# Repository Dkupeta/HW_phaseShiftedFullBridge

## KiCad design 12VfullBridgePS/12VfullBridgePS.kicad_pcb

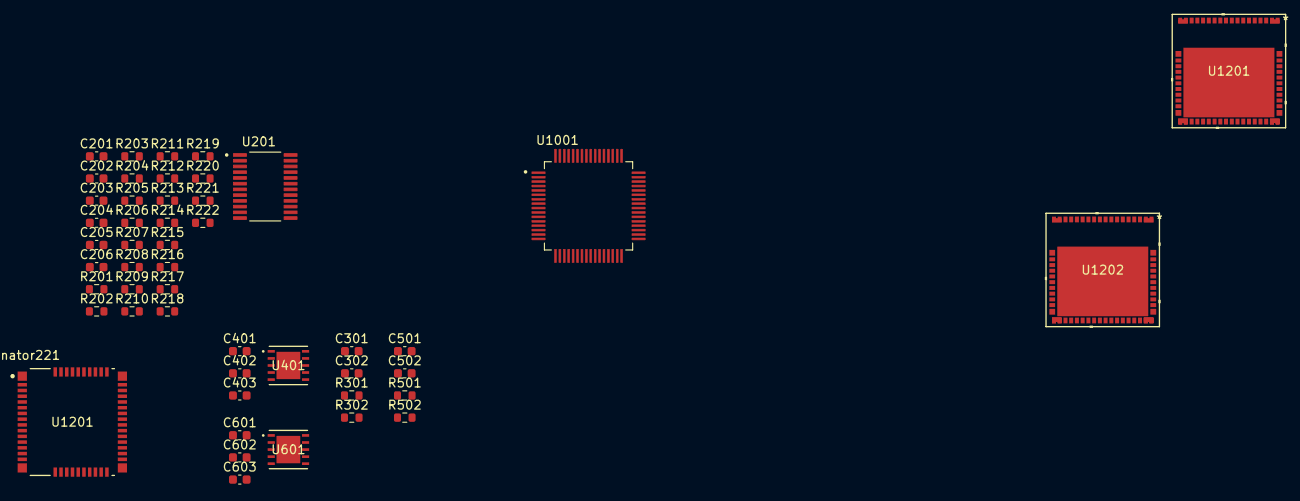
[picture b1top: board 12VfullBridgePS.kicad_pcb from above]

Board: 4 copper layers, 49 parts (0 on the bottom side), 33 nets, no tracks yet.

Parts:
C201: 330pF; C_0603_1608Metric
C202: 0.01uF; C_0603_1608Metric
C203, C206, C301, C401, C501, C601: 1uF; C_0603_1608Metric
C204: 0.047uF; C_0603_1608Metric
C205: 820pF; C_0603_1608Metric
C302, C402, C403, C502, C602, C603: 0.1uF; C_0603_1608Metric
R201, R218, R220: 10k; R_0603_1608Metric
R202: 10; R_0603_1608Metric
R203: 19.1k; R_0603_1608Metric
R204: 100; R_0603_1608Metric
R205: 18.2K; R_0603_1608Metric
R206: 1k; R_0603_1608Metric
R207, R208: 10K; R_0603_1608Metric
R209: 60.4K; R_0603_1608Metric
R210: 20K; R_0603_1608Metric
R211, R213, R215, R217, R219: DNP; R_0603_1608Metric
R212, R214, R216: 13k; R_0603_1608Metric
R221, R222, R301, R302, R501, R502: 0; R_0603_1608Metric
U201: UCC28951QPWRQ1
U401, U601: UCC27212AQDDARQ1; 8-PowerSOIC
U1001: F280048CPMQR; QFP50P1200X1200X160-64N
U1201: LMG3522R030QRQSRQ1; LMG3522R030QRQSRQ1-52-VQFN
U1201#2, U1202: XLMG3422R050RQZT; VQFN-54_12x12

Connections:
/DRV1/10V: C301.1, C302.1, C401.1, C402.1, C501.1, C502.1, C601.1, C603.1, U401.1 (VDD), U601.1 (VDD)
/DRV_E: R501.2, R502.2
/DRV_F: R301.2, R302.2
/PWMA: U201.22 (OUTA), U401.7 (HI)
/PWMC: U201.20 (OUTC), U601.7 (HI)
/PWMD: U201.19 (OUTD), U601.8 (LI)
/SW_AB: C403.1, U401.4 (HS)
/SW_CD: C602.1, U601.4 (HS)
/TMS_mcu/refGND: U1001.5 (VSS), U1001.21 (VSSA), U1001.26 (VSS), U1001.45 (VSS), U1001.55 (VSS_SW), U1001.58 (VSS)
/controller/ADEL: R217.1, R218.2, R221.1, U201.14 (ADEL)
/controller/ADELEF: R219.1, R220.2, R222.1, U201.13 (ADELEF)
/controller/CS_FLT: C205.2, R204.1, R221.2, R222.2, U201.15 (CS)
/controller/DCM: R203.1, R206.2, U201.12 (DCM)
/controller/DELAB: R215.1, R216.2, U201.6 (DELAB)
/controller/DELCD: R213.1, R214.2, U201.7 (DELCD)
/controller/DELEF: R211.1, R212.2, U201.8 (DELEF)
/controller/EA+: R207.2, R208.1, U201.2 (EA+)
/controller/VREF: C203.2, R203.2, R205.1, R207.1, R211.2, R213.2, R215.2, R217.2, R219.2, U201.1 (VREF)
FB: C201.2, C202.2, U201.3 (EA-)
GNDREF: C201.1, C203.1, C204.1, C205.1, C206.2, C301.2, C302.2, C401.2, C402.2, C501.2, C502.2, C601.2, C603.2, R201.1, R206.1, R208.2, R209.2, R210.1, R212.1, R214.1, R216.1, R218.1, R220.1, U201.4 (COMP), U201.21 (OUTB), U201.24 (GND), U401.8 (LI), U401.9 (VSS), U401.11 (POWERPAD), U601.9 (VSS), U601.11 (POWERPAD)
unnamed: C202.1, R201.2
unnamed: R210.2, U201.11 (RSUM)
unnamed: R205.2, U201.10 (RT)
unnamed: C204.2, U201.5 (SS_EN)
unnamed: R209.1, U201.9 (TMIN)
unnamed: C206.1, R202.2, U201.23 (VDD)
unnamed: C403.2, U401.2 (HB)
unnamed: C602.2, U601.2 (HB)
unnamed: U1001.4 (VDD), U1001.27 (VDD), U1001.44 (VDD), U1001.59 (VDD)
unnamed: U1001.28 (VDDIO), U1001.43 (VDDIO), U1001.60 (VDDIO)
unnamed: U1201#2.1 (DRAIN), U1201#2.2 (DRAIN), U1201#2.3 (DRAIN), U1201#2.4 (DRAIN), U1201#2.5 (DRAIN), U1201#2.6 (DRAIN), U1201#2.7 (DRAIN), U1201#2.8 (DRAIN), U1201#2.9 (DRAIN), U1201#2.10 (DRAIN), U1201#2.11 (DRAIN), U1201#2.12 (DRAIN), U1201#2.13 (DRAIN), U1201#2.14 (DRAIN), U1201#2.15 (DRAIN), U1201#2.16 (DRAIN)
unnamed: U1201#2.17 (SOURCE), U1201#2.18 (SOURCE), U1201#2.19 (SOURCE), U1201#2.20 (SOURCE), U1201#2.21 (SOURCE), U1201#2.22 (SOURCE), U1201#2.23 (SOURCE), U1201#2.24 (SOURCE), U1201#2.25 (SOURCE), U1201#2.26 (SOURCE), U1201#2.27 (SOURCE), U1201#2.28 (SOURCE), U1201#2.29 (SOURCE), U1201#2.30 (SOURCE), U1201#2.31 (SOURCE), U1201#2.32 (SOURCE), U1201#2.33 (SOURCE), U1201#2.34 (SOURCE), U1201#2.35 (SOURCE), U1201#2.36 (SOURCE), U1201#2.37 (SOURCE), U1201#2.38 (SOURCE), U1201#2.39 (SOURCE), U1201#2.40 (SOURCE), U1202.1 (DRAIN), U1202.2 (DRAIN), U1202.3 (DRAIN), U1202.4 (DRAIN), U1202.5 (DRAIN), U1202.6 (DRAIN), U1202.7 (DRAIN), U1202.8 (DRAIN), U1202.9 (DRAIN), U1202.10 (DRAIN), U1202.11 (DRAIN), U1202.12 (DRAIN), U1202.13 (DRAIN), U1202.14 (DRAIN), U1202.15 (DRAIN), U1202.16 (DRAIN)
unnamed: U1202.17 (SOURCE), U1202.18 (SOURCE), U1202.19 (SOURCE), U1202.20 (SOURCE), U1202.21 (SOURCE), U1202.22 (SOURCE), U1202.23 (SOURCE), U1202.24 (SOURCE), U1202.25 (SOURCE), U1202.26 (SOURCE), U1202.27 (SOURCE), U1202.28 (SOURCE), U1202.29 (SOURCE), U1202.30 (SOURCE), U1202.31 (SOURCE), U1202.32 (SOURCE), U1202.33 (SOURCE), U1202.34 (SOURCE), U1202.35 (SOURCE), U1202.36 (SOURCE), U1202.37 (SOURCE), U1202.38 (SOURCE), U1202.39 (SOURCE), U1202.40 (SOURCE)

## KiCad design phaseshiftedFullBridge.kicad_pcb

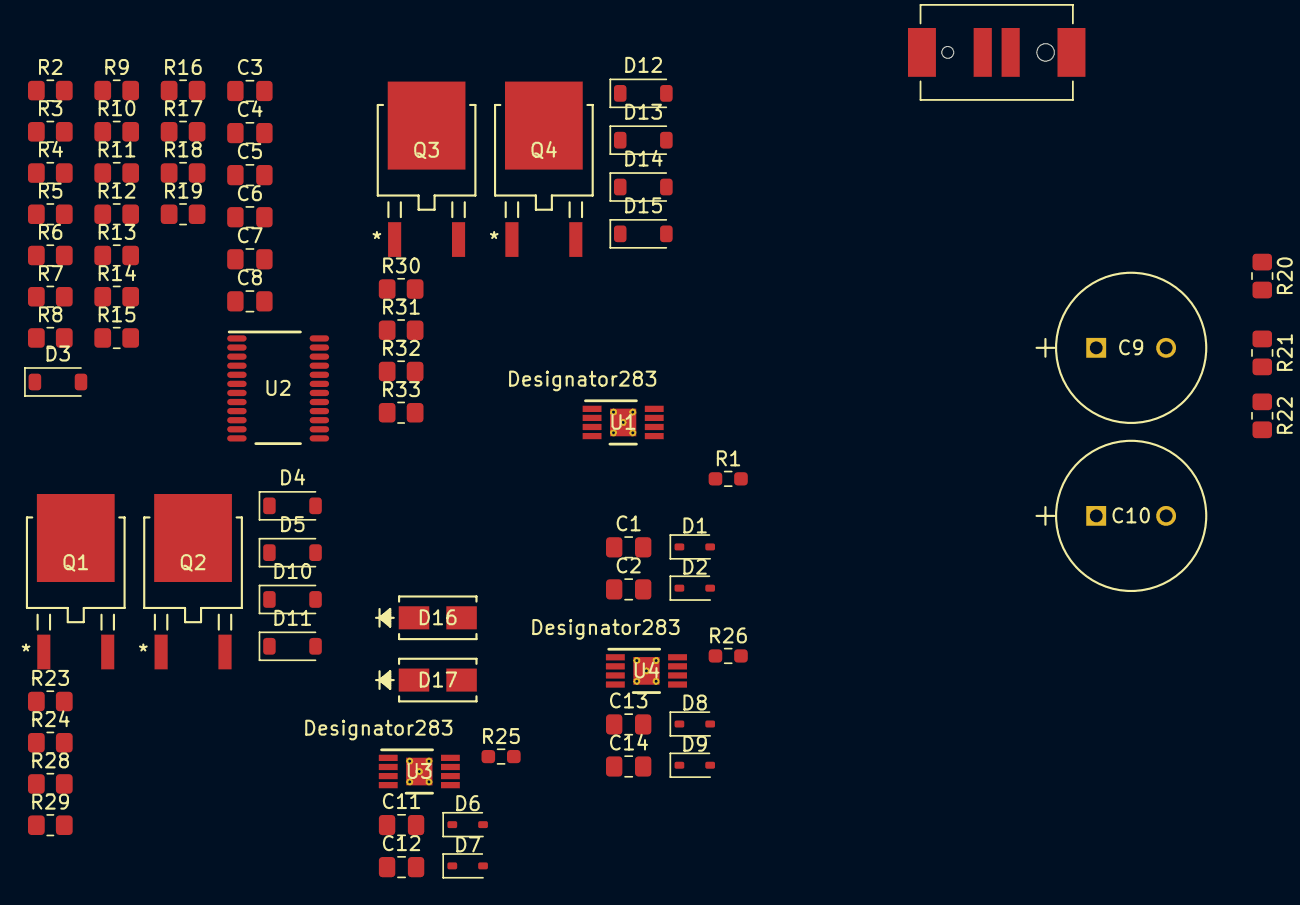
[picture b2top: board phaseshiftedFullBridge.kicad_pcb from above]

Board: 4 copper layers, 72 parts (0 on the bottom side), 54 nets, no tracks yet.

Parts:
C1, C12, C14: 1 µF; C_0805_2012Metric_Pad1.18x1.45mm_HandSolder
C2, C7, C11, C13: 1uF; C_0805_2012Metric_Pad1.18x1.45mm_HandSolder
C3, C6: 100nF; C_0805_2012Metric_Pad1.18x1.45mm_HandSolder
C4: 56nF; C_0805_2012Metric_Pad1.18x1.45mm_HandSolder
C5: 5.6nF; C_0805_2012Metric_Pad1.18x1.45mm_HandSolder
C8: 470pF; C_0805_2012Metric_Pad1.18x1.45mm_HandSolder
C9, C10: C_Polarized; Radial-Can-THT
D1, D2, D6, D7, D8, D9: BAT54WS; BAT54WS-P36_SOD-323F
D3: D; D_SOD-123
D4, D10, D12, D14: MMSD4148T1G; D_SOD-123
D5, D11, D13, D15: MMSZ5242B-7-F; D_SOD-123
D16, D17: US1G-E3/5AT; D_DO214AC
J2: 10159560-200421RLF; AMPHENOL_10159560-200421RLF
Q1, Q2, Q3, Q4: STD3NK80ZT4; DPAK_STM
R1, R25, R26: 3R01; R_0603_1608Metric_Pad0.98x0.95mm_HandSolder
R2: 2.94k; R_0805_2012Metric_Pad1.20x1.40mm_HandSolder
R3, R4: 2.37k; R_0805_2012Metric_Pad1.20x1.40mm_HandSolder
R5, R6, R7: 8.25k; R_0805_2012Metric_Pad1.20x1.40mm_HandSolder
R8: 11k; R_0805_2012Metric_Pad1.20x1.40mm_HandSolder
R9, R17: 1k; R_0805_2012Metric_Pad1.20x1.40mm_HandSolder
R10: 13k; R_0805_2012Metric_Pad1.20x1.40mm_HandSolder
R11: 18.7k; R_0805_2012Metric_Pad1.20x1.40mm_HandSolder
R12: 133k; R_0805_2012Metric_Pad1.20x1.40mm_HandSolder
R13: 59k; R_0805_2012Metric_Pad1.20x1.40mm_HandSolder
R14, R15, R16: 75k; R_0805_2012Metric_Pad1.20x1.40mm_HandSolder
R18: 1.91k; R_0805_2012Metric_Pad1.20x1.40mm_HandSolder
R19: 205k; R_0805_2012Metric_Pad1.20x1.40mm_HandSolder
R20, R21, R22: R; R_0805_2012Metric_Pad1.20x1.40mm_HandSolder
R23, R28, R30, R31: 3.01; R_0805_2012Metric_Pad1.20x1.40mm_HandSolder
R24, R29, R32, R33: 10k; R_0805_2012Metric_Pad1.20x1.40mm_HandSolder
U1, U3, U4: UCC27424QDGNRQ1; DGN0008B_N
U2: UCC28950QPWRQ1; PW0024A_N

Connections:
/UCC27324P1/INa: U2.20 (OUTC), U3.2 (INA)
/UCC27324P1/INb: U2.19 (OUTD), U3.4 (INB)
/UCC27324P1/OUTb: D6.2 (C), U3.5 (OUTB)
/UCC27324P2/INa: U2.18 (OUTE), U4.2 (INA)
/UCC27324P2/INb: U2.17 (OUTF), U4.4 (INB)
/UCC27324P2/OUTb: D8.2 (C), U4.5 (OUTB)
/UCC27324P/INa: U1.2 (INA), U2.22 (OUTA)
/UCC27324P/INb: U1.4 (INB), U2.21 (OUTB)
/UCC27324P/OUTb: D2.2 (C), U1.5 (OUTB)
/controller/Vb: D3.2 (A), R19.2
/rectif1/Lout: D13.2 (A), Q3.3 (S), Q4.2 (D), R32.2
/rectif/Lout: D5.2 (A), Q1.3 (S), Q2.2 (D), R24.2
/rectif/Vin: D16.1 (K), Q1.2 (D), Q3.2 (D)
Earth: C9.2, C10.2, J2.1, R22.2
GND: C2.2, C6.2, C7.2, C8.2, C11.2, C13.2, D1.1 (A), D2.1 (A), D6.1 (A), D7.1 (A), D8.1 (A), D9.1 (A), D11.2 (A), D15.2 (A), Q2.3 (S), Q4.3 (S), R6.2, R7.2, R9.2, R11.1, R12.1, R14.1, R15.1, R16.1, R18.1, R19.1, R29.2, R33.2, U1.3 (GND), U3.3 (GND), U4.3 (GND)
unnamed: C1.1, R1.2
unnamed: C4.1, R2.2
unnamed: C4.2, C5.2
unnamed: C9.1, C10.1, J2.2, R20.1
unnamed: C12.1, R25.2
unnamed: C14.1, R26.2
unnamed: D1.2 (C), R1.1, U1.7 (OUTA)
unnamed: D3.1 (K), R17.2, R18.2
unnamed: D4.2 (A), Q1.1 (G), R23.2, R24.1
unnamed: D4.1 (K), D5.1 (K)
unnamed: D7.2 (C), R25.1, U3.7 (OUTA)
unnamed: D9.2 (C), R26.1, U4.7 (OUTA)
unnamed: D10.2 (A), Q2.1 (G), R28.2, R29.1
unnamed: D10.1 (K), D11.1 (K)
unnamed: D12.2 (A), Q3.1 (G), R30.2, R32.1
unnamed: D12.1 (K), D13.1 (K)
unnamed: D14.2 (A), Q4.1 (G), R31.2, R33.1
unnamed: D14.1 (K), D15.1 (K)
unnamed: D16.2 (A), D17.1 (K)
unnamed: R3.2, R4.1
unnamed: R20.2, R21.1
unnamed: R21.2, R22.1
unnamed: C2.1, U1.6 (VDD)
unnamed: R7.1, R8.2, U2.14 (ADEL)
unnamed: R5.2, R6.1, U2.13 (ADELEF)
unnamed: C5.1, R2.1, U2.4 (COMP)
unnamed: C8.1, R5.1, R8.1, R17.1, U2.15 (CS)
unnamed: R9.1, R10.2, U2.12 (DCM)
unnamed: R16.2, U2.6 (DELAB)
unnamed: R15.2, U2.7 (DELCD)
unnamed: R14.2, U2.8 (DELEF)
unnamed: R12.2, U2.11 (RSUM)
unnamed: R13.1, U2.10 (RT)
unnamed: C6.1, U2.5 (SS_EN)
unnamed: R11.2, U2.9 (TMIN)
unnamed: C7.1, U2.23 (VDD)
unnamed: C3.1, R3.1, U2.1 (VREF)
unnamed: C11.1, U3.6 (VDD)
unnamed: C13.1, U4.6 (VDD)

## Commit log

2024-06-22 add initial work
2024-08-05 edit to proj
2024-08-24 add new 12V project
2024-08-24 ADD 3V3 1V2 BUCK DETAIL
2025-01-12 edits from HP15s
